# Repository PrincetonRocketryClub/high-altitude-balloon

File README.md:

# High Altitude Balloon
High Altitude Balloon for the Global Space Balloon Challenge.

Electronics without battery is 70 grams, battery is 98 grams.

## Controller
The primary microcontroller used is a [Teensy 3.5](https://www.pjrc.com/store/teensy35.html). The Teensy is a Arduino-compatible ARM based development board. 

Software will be based on the [Trackuino project](https://github.com/trackuino/trackuino) with modifications for Teensy DAC support from [this project.](https://github.com/rvnash/aprs_teensy31)

## Communications
Telemetry will be sent via 2m APRS using the [HX1 2m Transmitter](http://www.radiometrix.com/content/hx1). This module has an output power of ~300mW tuned to a frequency of 144.390 MHz. There are reports of frequency drift with temperature, so this behavior will have to be characterized before launch.

Antenna will be a simple half-wavelength dipole, likely based on [this](http://bear.sbszoo.com/construction/antenna/cf/hwcf2.htm) or [this.](http://bear.sbszoo.com/construction/antenna/cf/hwcf1.htm)

### APRS Message Format
Use standard headers etc. Symbol `/O` (Primay symbol table, symbol ID 'O' corresponding to balloon). Message type based on "Lat/Long Position Report Format — with Data Extension and Timestamp" in the [APRS spec](http://www.aprs.org/doc/APRS101.PDF).

String:
`[Data Type ID flag:/]HHMMSSh[Latitude ddmm.hh[N/S](8b)][SymtableID (1b)][Longitude dddmm.hh[W/E](9b)][Symbol Code (1b)][Course/Speed (7b)][Arb. data (36b)]`  

### Comment format
Chars | Description | Example
----- | ----------- | -------
5 | Timestamp (sec) | 12000
1 | Separator | ,
5 | BMP180 Temperature (C) | -60.0
1 | Separator | ,
6 | BMP180 Pressure (Pa) | 101580
1 | Separator | ,
4 | Thermistor ADC Value, max 1023 | 1017
23 | Total |

### HX-1 Transmitter
- [Main Page](http://www.radiometrix.com/content/hx1)

Pinout

Pin Label | Functionality | Connection
--------- | ------------- | ----------
1, 3 | RF Ground | SMA Shield
2 | RF out | SMA Center pin
4 | Active-high Enable | Digital pin 11
5 | 5V Supply | N/A
6 | GND | N/A
7 | TX Data | DAC1

# Sensors
## U-Blox MAX-M8 GPS Receiver
### Datasheets
- [Breakout Board](https://store.uputronics.com/?route=product/product&product_id=72)
- [Hardware Specs](https://www.u-blox.com/sites/default/files/MAX-M8-FW3_DataSheet_%28UBX-15031506%29.pdf)
- [Protocol Spec](https://www.u-blox.com/sites/default/files/products/documents/u-blox8-M8_ReceiverDescrProtSpec_%28UBX-13003221%29_Public.pdf)

### Software
Outputs NEMA strings over serial, so should integrate with Trackuino's code nicely. Might have to do some configuration via UART. See page 175 of protocol spec for NMEA config. 

Config example code: http://playground.arduino.cc/UBlox/GPS
Other tutorial: http://ava.upuaut.net/?p=738

The settings we'll need:
- Set non-GPS source's ID's to GPGGA for compatibility
- Double check all available sources are enabled
- Disable some unnecessary debug outputs
- Figure out how to switch between low and high altitude mode
- Change refresh rate

### I/O
Pin Label | Functionality | Connection
--------- | ------------- | ----------
SDA | I2C | N/A
SCL | I2C | N/A 
TXD | Serial UART | Serial4 RX
RXD | Serial UART | Serial4 TX
GND | Ground | 
VCC | 3.3V Power | 

## BMP180 Barometer/Temperature
### Datasheets
- [Adafruit](https://www.adafruit.com/products/1603)
- [Library](https://learn.sparkfun.com/tutorials/bmp180-barometric-pressure-sensor-hookup-/installing-the-arduino-library)

### Software
Use the Sparkfun library. Communicates over I2C, nothing fancy. Must use SCL/SDA0 since those correspond to the default Wire interface.

### I/O
Pin Label | Functionality | Connection
--------- | ------------- | ----------
VIN | 5V power in, feeds on-board regulator | N/A
3V3 | 3V3 power rail | N/A 
GND | Ground | Black
SCL | I2C | SCL0 (Pin 19)
SDA | I2C | SDA0 (Pin 18)

## MMA8451 3-axis accelerometer
### Datasheets
- [Adafruit](https://www.adafruit.com/product/2019)
- [Library](https://learn.adafruit.com/adafruit-mma8451-accelerometer-breakout/wiring-and-test)

### Software
Use the Adafruit library. Communicates over I2C.

### I/O
Pin Label | Functionality | Wire Color
--------- | ------------- | ----------
VIN | 5V power in, feeds on-board regulator | NC
3Vo | 3V3 power rail | N/A 
GND | Ground | Black
SCL | I2C | SCL0 (Pin 19)
SDA | I2C | SDA0 (Pin 18)
A | Address Select | NC for address 0x1C
I1 | Interrupt 1 | NC
I2 | Interrupt 2 | NC

## 3950 NTC Thermristor
### Datasheets
- [Adafruit](https://www.adafruit.com/product/372)
- [Tutorial](https://learn.adafruit.com/thermistor/using-a-thermistor)
- [Lookup Table](https://cdn-shop.adafruit.com/datasheets/103_3950_lookuptable.pdf)

Hook it up with a 10k resistor in a voltage divider setup, read with ADC. Connected to ADC17

# Actuators

## Electric heating pad

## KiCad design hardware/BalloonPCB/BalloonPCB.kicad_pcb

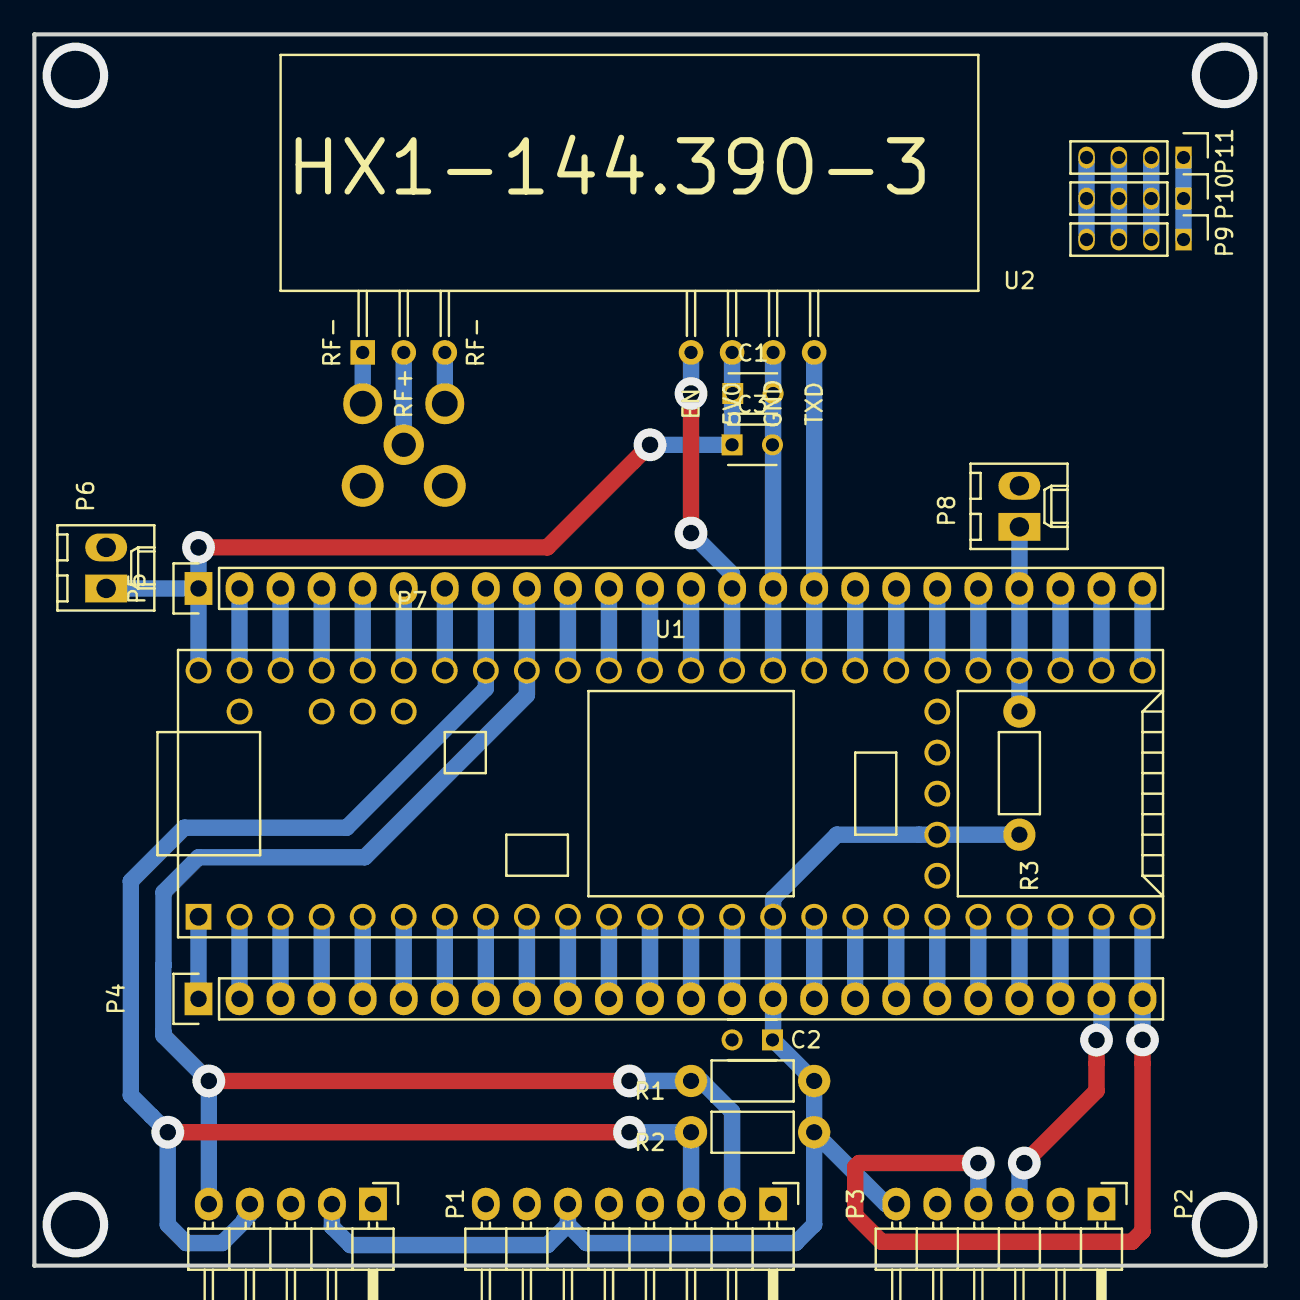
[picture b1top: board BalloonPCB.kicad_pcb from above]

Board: 2 copper layers, 76.2 x 76.2 mm, 19 parts (0 on the bottom side), 51 nets.

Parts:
C1, C2, C3: 0.1uF; C_Disc_D3_P2.5
P1: BMP180_HEADER; Pin_Header_Angled_1x05
P2: GPS_HEADER; Pin_Header_Angled_1x06
P3: ACCEL_HEADER; Pin_Header_Angled_1x08
P4, P5: CONN_01X24; Pin_Header_Straight_1x24
P6: 5VDC_HEADER; Molex_KK-6410-02_02x2.54mm_Straight
P7: SMA; SMA_Socket_TYCO-AMP
P8: THERMO_HEADER; Molex_KK-6410-02_02x2.54mm_Straight
P9, P10, P11: CONN_01X04; Pin_Header_Straight_1x04_Pitch2.00mm
R1, R2: 3.3k; Resistor_Horizontal_RM7mm
R3: 10k; Resistor_Horizontal_RM7mm
U1: Teensy3.5; Teensy35_36
U2: HX1

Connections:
+3V3: C2.1, P1.2, P2.6, P3.6, P4.15, P5.3, R1.1, R2.1, R3.1, U1.15, U1.26, U1.51
+5V: C1.1, C3.1, P5.1, P6.1, U1.53, U2.5
GND: C1.2, C2.2, C3.2, P1.3, P2.5, P3.7, P4.1, P5.15, P6.2, P7.2, P8.2, U1.1, U1.27, U1.39, U2.1, U2.3, U2.6
GPS_RXD: P2.4, P4.24, U1.24
GPS_TXD: P2.3, P4.23, U1.23
unnamed: P4.2, U1.2
unnamed: P4.3, U1.3
unnamed: P4.4, U1.4
unnamed: P4.7, U1.7
unnamed: P4.8, U1.8
unnamed: P4.9, U1.9
unnamed: P4.10, U1.10
unnamed: P4.11, U1.11
unnamed: P4.12, U1.12
unnamed: P4.13, U1.13
unnamed: P4.14, U1.14
unnamed: P4.16, U1.16
unnamed: P4.17, U1.17
unnamed: P4.18, U1.18
unnamed: P4.19, U1.19
unnamed: P4.20, U1.20
unnamed: P4.21, U1.21
unnamed: P4.22, U1.22
unnamed: P5.2, U1.52
unnamed: P5.4, U1.50
unnamed: P5.5, U1.49
unnamed: P5.6, U1.48
unnamed: P5.7, U1.47
unnamed: P5.10, U1.44
unnamed: P5.11, U1.43
unnamed: P5.12, U1.42
unnamed: P5.13, U1.41
unnamed: P5.17, U1.37
unnamed: P5.18, U1.36
unnamed: P5.19, U1.35
unnamed: P5.20, U1.34
unnamed: P5.21, P8.1, R3.2, U1.33
unnamed: P5.22, U1.32
unnamed: P5.23, U1.31
unnamed: P5.24, U1.30
unnamed: P9.1, P10.1, P11.1
unnamed: P9.2, P10.2, P11.2
unnamed: P9.3, P10.3, P11.3
unnamed: P9.4, P10.4, P11.4
RF+: P7.1, U2.2
SCL0: P1.4, P3.3, P5.8, R2.2, U1.46
SCL2: P4.5, U1.5
SDA0: P1.5, P3.2, P5.9, R1.2, U1.45
SDA2: P4.6, U1.6
TXD: P5.16, U1.38, U2.7
TX_EN: P5.14, U1.40, U2.4

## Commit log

2017-02-04 Create LICENSE
2017-02-04 Add files from aprs_teensy31
2017-02-04 Add pinmap
2017-02-05 Fix HX1 pin table
2017-02-15 Add KiCAD project, Teensy lib
2017-02-24 Change to Arduino file type
2017-02-24 Update GPS code
2017-03-02 Major cleanup, refactoring of APRS code
2017-03-09 Add GPS raw serial data for debugging
2017-03-11 Started PCB layout
2017-03-11 First routing pass, everything except radio
2017-03-11 PCB signals routed
2017-03-18 Board fully routed, add decoupling caps
2017-03-18 Add pours
2017-03-19 Add spot for thermristor
2017-03-20 Add prototyping section
2017-03-20 First revision export
2017-03-20 Update to reflect PCB
2017-03-20 Update pin configuration documentation
2017-03-20 Change to pull tx enable pin low on start
2017-03-20 Many typo and type fixes, code now compiles
2017-03-24 Fix serial baud rates
2017-03-24 Command formats exported from u-central
2017-04-02 Add bmp180 test sketch
2017-04-10 Add ublox config code
2017-04-11 Field trials, fix PTT pin number, still debugging ublox code
2017-04-11 Add UBlox example code, which works
2017-04-15 Fixed Ublox config, add DAC output recordings
2017-04-15 Finish ublox config code
2017-04-15 Add BMP180 code, rename TinyGPS to fix IDE detect
2017-04-15 Add thermistor code
2017-04-15 Update APRS symbol id to balloon
2017-04-16 Add SD functionality, fill in APRS comment
2017-04-16 Add GPS mode switching based on altitude (untested)
2017-04-16 Live test result
2017-04-27 Add Antenna Board design
2017-05-17 Fix longitude/latitude conversion bug
2017-05-17 Add dynamic APRS transmission rate
2017-10-18 Add board photos
2017-12-06 Add data from flight
2017-12-27 Fix copyrights
